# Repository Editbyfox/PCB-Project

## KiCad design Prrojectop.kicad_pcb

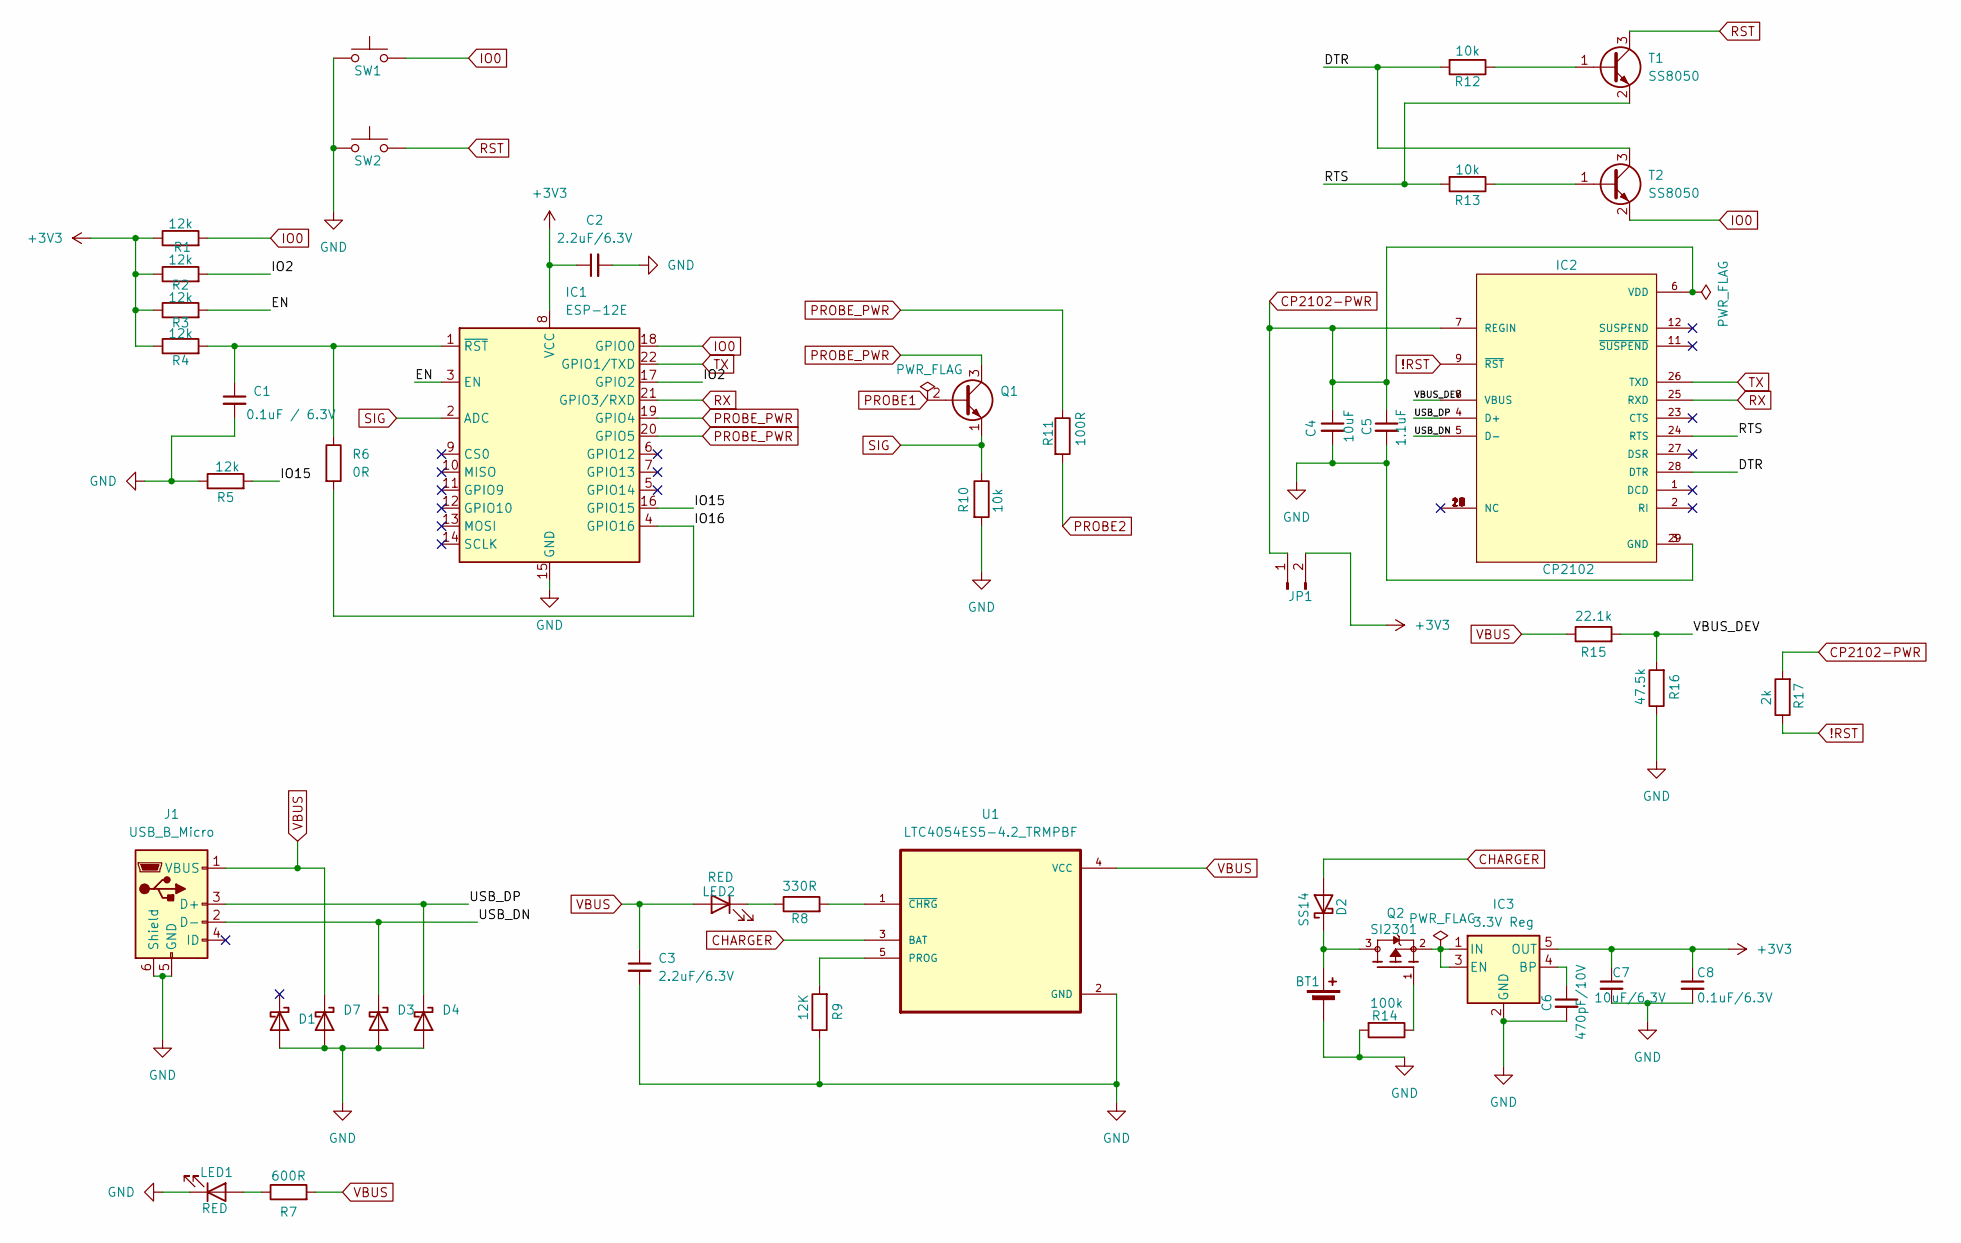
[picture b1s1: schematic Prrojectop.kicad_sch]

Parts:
BT1: Battery_Cell; BatteryHolder_Keystone_2460_1xAA
C1: 0.1uF / 6.3V; CP_EIA-1608-08_AVX-J
C2, C3: 2.2uF/6.3V; CP_EIA-1608-08_AVX-J
C4: 10uF; CP_EIA-1608-08_AVX-J
C5: 1.1uF; CP_EIA-1608-08_AVX-J
C6: 470pF/10V; CP_EIA-1608-08_AVX-J
C7: 10uF/6.3V; CP_EIA-1608-08_AVX-J
C8: 0.1uF/6.3V; CP_EIA-1608-08_AVX-J
D1, D3, D4, D7: SB120; D_SOD-123F
D2: SS14; D_SMA
IC1: ESP-12E
IC2: CP2102; QFN50P500X500X100-29N
IC3: 3.3V Reg; SOT-23-5
J1: USB_B_Micro; USB_Micro-B_Molex_47346-0001
JP1: Conn_01x02_Pin; PinHeader_1x02_P2.54mm_Vertical_SMD_Pin1Left
LED1, LED2: RED; LED_D3.0mm
Q1: 2N3904; TO-92_Inline
Q2: SI2301; DESTO_SOT23
R1, R2, R3, R4, R5: 12k; R_0805_2012Metric_Pad1.20x1.40mm_HandSolder
R6: 0R; R_0805_2012Metric_Pad1.20x1.40mm_HandSolder
R7: 600R; R_0805_2012Metric_Pad1.20x1.40mm_HandSolder
R8: 330R; R_0805_2012Metric_Pad1.20x1.40mm_HandSolder
R9: 12K; R_0805_2012Metric_Pad1.20x1.40mm_HandSolder
R10, R12, R13: 10k; R_0805_2012Metric_Pad1.20x1.40mm_HandSolder
R11: 100R; R_0805_2012Metric_Pad1.20x1.40mm_HandSolder
R14: 100k; R_0805_2012Metric_Pad1.20x1.40mm_HandSolder
R15: 22.1k; R_0805_2012Metric_Pad1.20x1.40mm_HandSolder
R16: 47.5k; R_0805_2012Metric_Pad1.20x1.40mm_HandSolder
R17: 2k; R_0805_2012Metric_Pad1.20x1.40mm_HandSolder
SW1, SW2: SW_Push; SW_Push_1TS009xxxx-xxxx-xxxx_6x6x5mm
T1, T2: SS8050; SOT-23
U1: LTC4054ES5-4.2_TRMPBF; SOT95P280X100-5N

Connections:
!RST: IC2.9 (~RST), R17.1
+3V3: C2.1, C7.1, C8.1, IC1.8 (VCC), IC3.5 (OUT), JP1.2, R1.1, R2.1, R3.1, R4.1
/DTR: IC2.28 (DTR), R12.2, T2.3 (C)
/EN: IC1.3 (EN), R3.2
/IO2: IC1.17 (GPIO2), R2.2
/IO15: IC1.16 (GPIO15), R5.2
/IO16: IC1.4 (GPIO16), R6.2
/RTS: IC2.24 (RTS), R13.2, T1.2 (E)
/USB_DN: D3.1 (K), IC2.5 (D-), J1.2 (D-)
/USB_DP: D4.1 (K), IC2.4 (D+), J1.3 (D+)
/VBUS_DEV: IC2.8 (VBUS), R15.2, R16.2
CHARGER: D2.2 (A), U1.3 (BAT)
CP2102-PWR: C4.1, C5.1, IC2.6 (VDD), IC2.7 (REGIN), JP1.1, R17.2
GND: BT1.2 (-), C1.2, C2.2, C3.2, C4.2, C5.2, C6.2, C7.2, C8.2, D1.2 (A), D3.2 (A), D4.2 (A), D7.2 (A), IC1.15 (GND), IC2.3 (GND), IC2.29 (GND), IC3.2 (GND), J1.5 (GND), J1.6 (Shield), LED1.1 (K), R5.1, R9.1, R10.2, R14.2, R16.1, SW1.1, SW2.1, U1.2 (GND)
IO0: IC1.18 (GPIO0), R1.2, SW1.2, T2.2 (E)
unnamed: BT1.1 (+), D2.1 (K), Q2.3
unnamed: C1.1, IC1.1 (~RST), R4.2, R6.1
unnamed: C6.1, IC3.4 (BP)
unnamed: IC3.1 (IN), IC3.3 (EN), Q2.2
unnamed: LED1.2 (A), R7.1
unnamed: LED2.1 (K), R8.1
unnamed: Q2.1, R14.1
unnamed: R12.1, T1.1 (B)
unnamed: R13.1, T2.1 (B)
unnamed: R9.2, U1.5 (PROG)
unnamed: R8.2, U1.1 (~CHRG)
PROBE1: Q1.2 (B)
PROBE2: R11.2
PROBE_PWR: IC1.19 (GPIO4), IC1.20 (GPIO5), Q1.3 (C), R11.1
RST: SW2.2, T1.3 (C)
RX: IC1.21 (GPIO3/RXD), IC2.25 (RXD)
SIG: IC1.2 (ADC), Q1.1 (E), R10.1
TX: IC1.22 (GPIO1/TXD), IC2.26 (TXD)
VBUS: C3.1, D7.1 (K), J1.1 (VBUS), LED2.2 (A), R7.2, R15.1, U1.4 (VCC)

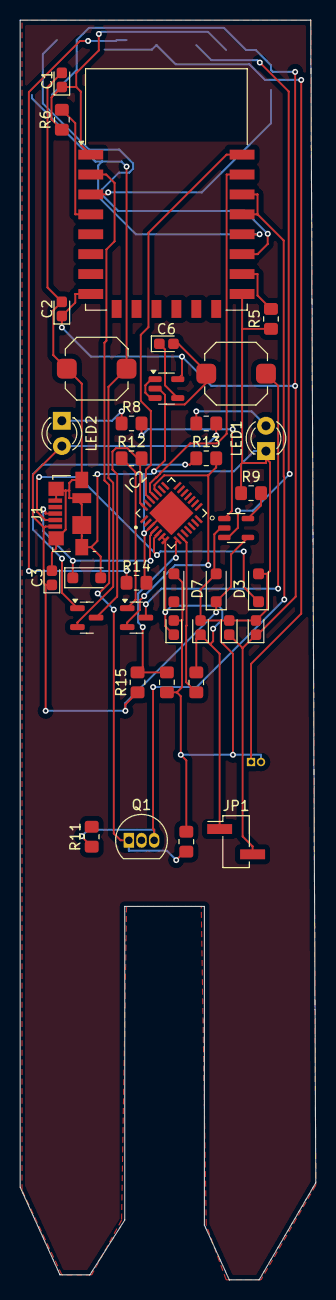
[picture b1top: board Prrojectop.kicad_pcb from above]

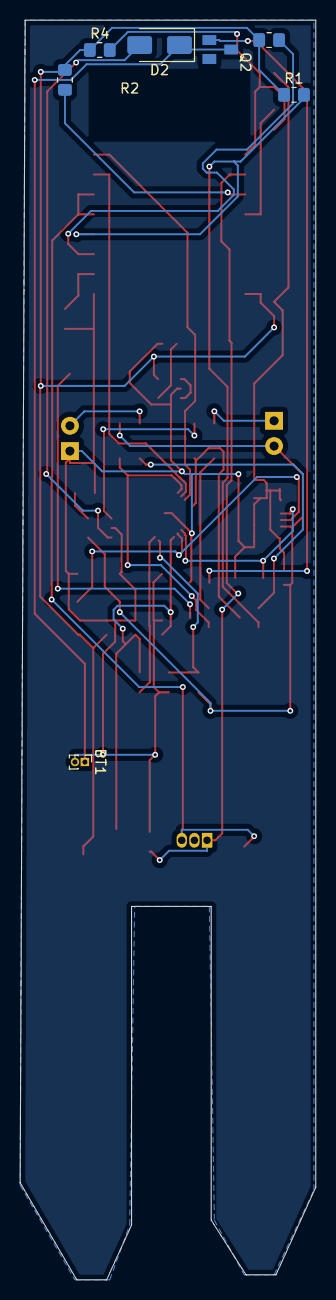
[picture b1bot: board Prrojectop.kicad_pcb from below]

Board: 2 copper layers, 29.7 x 126.5 mm, 45 parts (7 on the bottom side), 32 nets.
